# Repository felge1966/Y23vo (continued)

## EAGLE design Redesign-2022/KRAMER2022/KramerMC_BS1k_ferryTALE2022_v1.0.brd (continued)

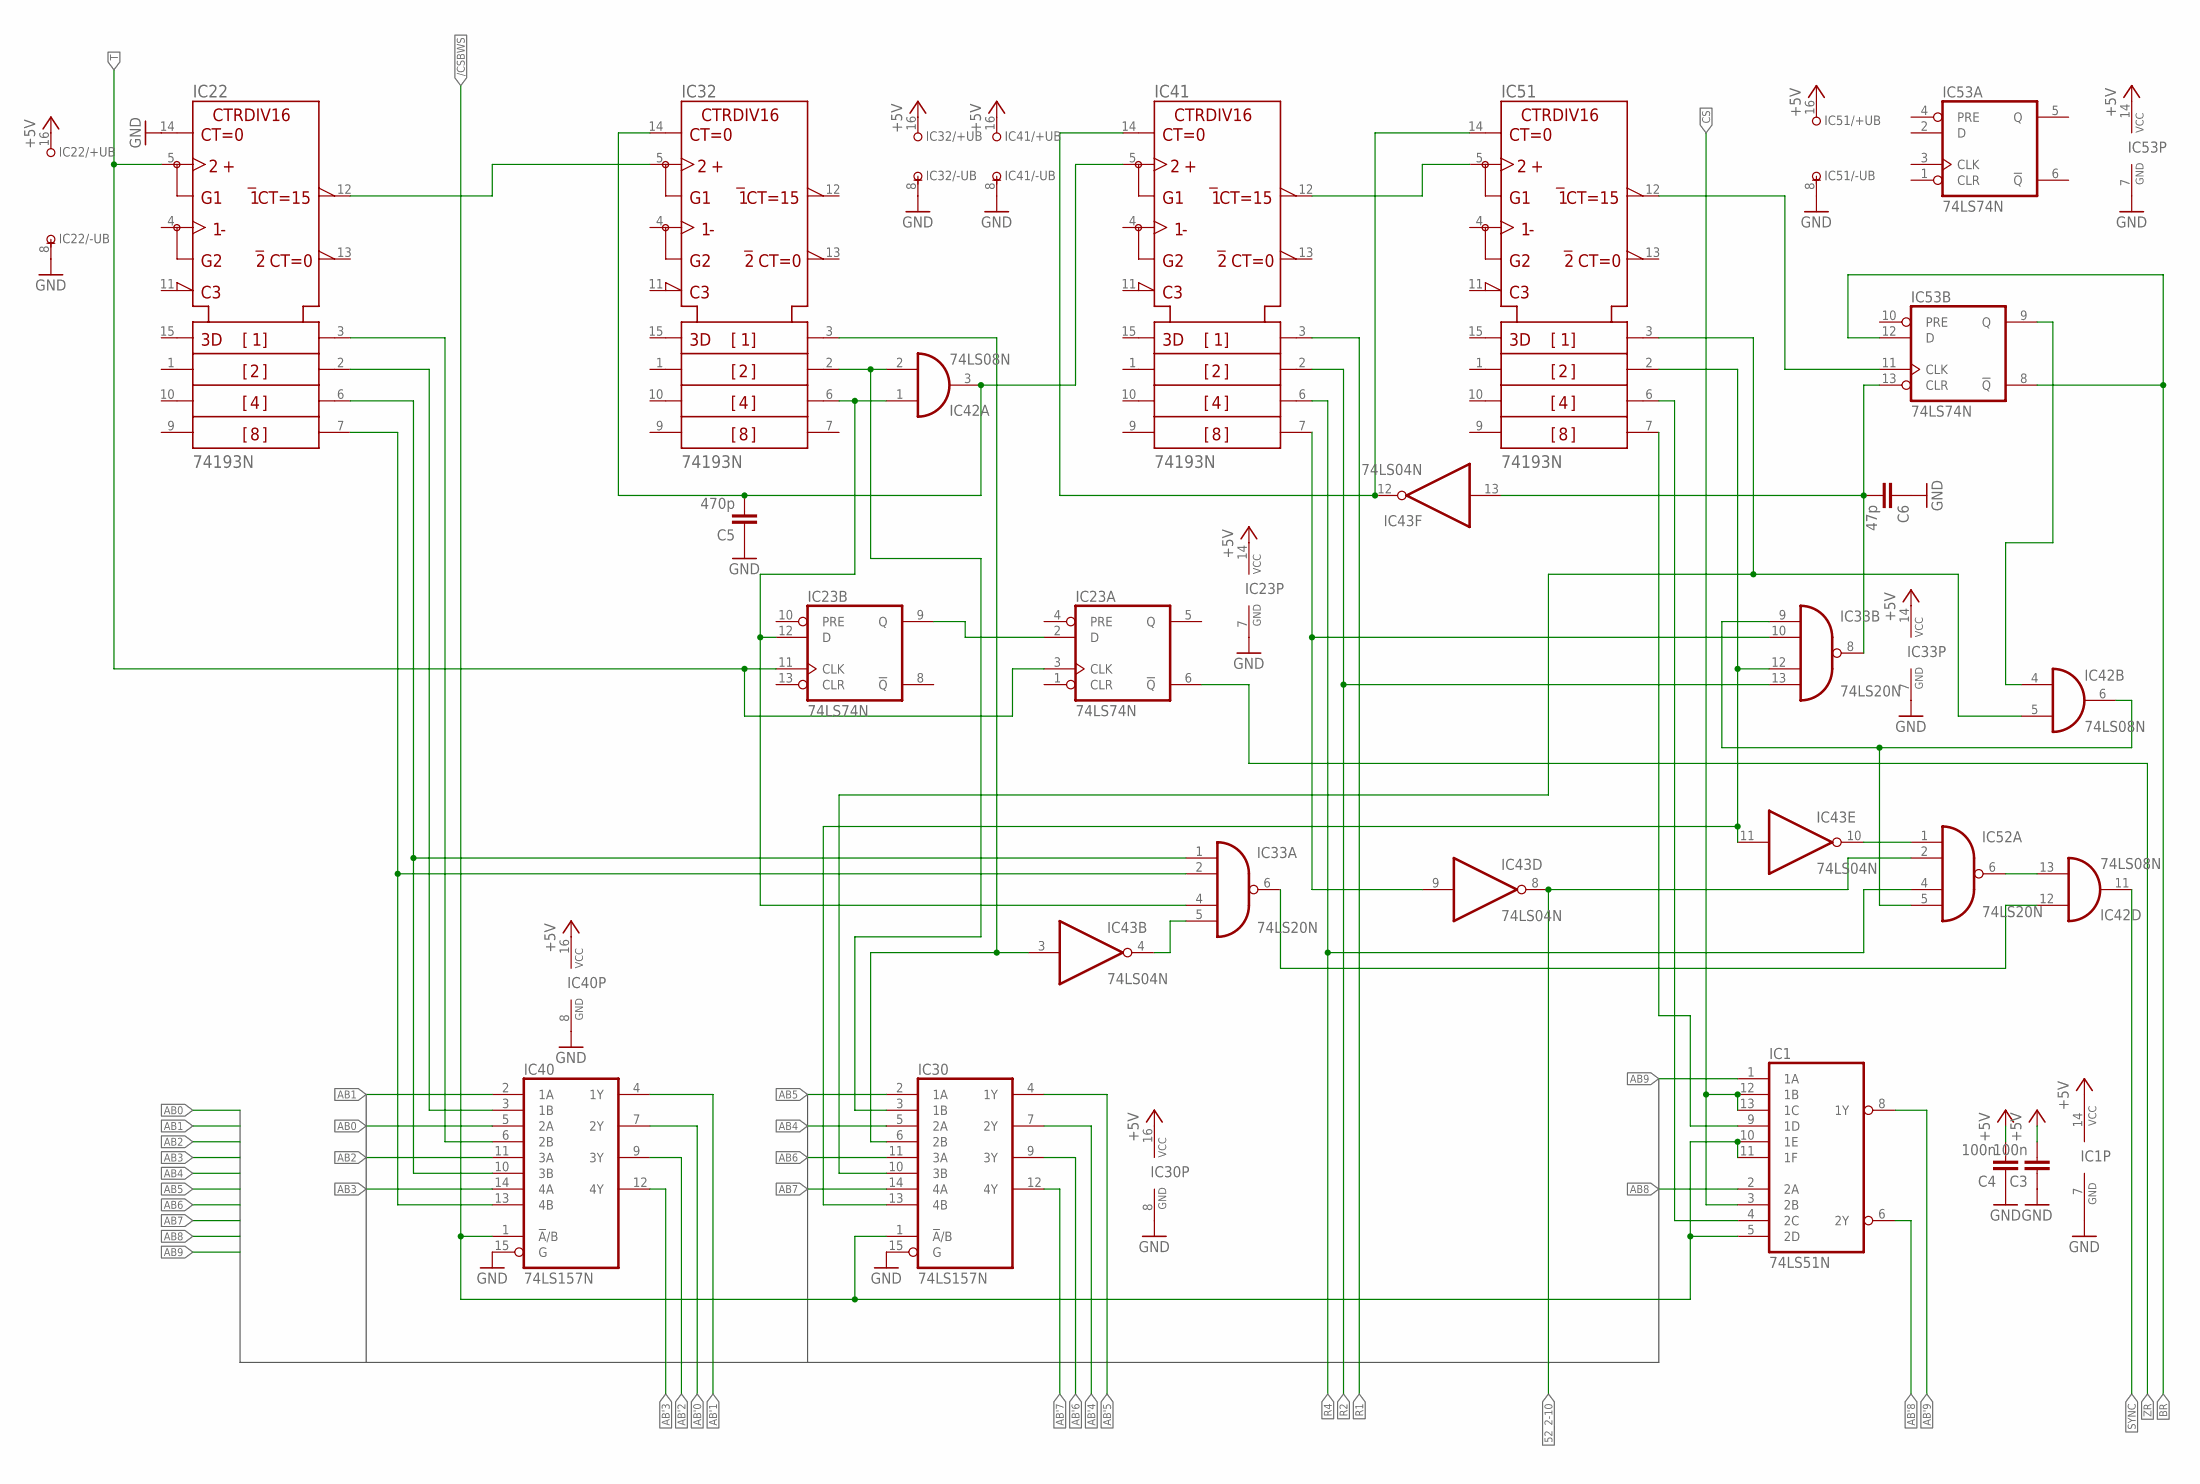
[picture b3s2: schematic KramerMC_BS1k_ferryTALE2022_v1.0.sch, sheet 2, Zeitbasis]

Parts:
C3, C4: 100n; C050-024X044
C5: 470p; C050-024X044
C6: 47p; C050-024X044
IC1: 74LS51N; DIL14
IC22, IC32, IC41, IC51: 74193N; DIL16
IC23, IC53: 74LS74N; DIL14
IC30, IC40: 74LS157N; DIL16
IC33, IC52: 74LS20N; DIL14
IC42: 74LS08N; DIL14
IC43: 74LS04N; DIL14

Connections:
52_2-10: IC43.8 (O), IC52.2 (I1); also elsewhere on the board
+5V: C3.2, C4.2, IC1.14 (VCC), IC22.16 (+UB), IC23.14 (VCC), IC30.16 (VCC), IC32.16 (+UB), IC33.14 (VCC), IC40.16 (VCC), IC41.16 (+UB), IC51.16 (+UB), IC53.14 (VCC); also elsewhere on the board
/CSBWS: IC1.5 (2D), IC1.10 (1E), IC1.11 (1F), IC30.1 (!A!/B), IC40.1 (!A!/B); also elsewhere on the board
AB0: IC40.5 (2A); also elsewhere on the board
AB1: IC40.2 (1A); also elsewhere on the board
AB2: IC40.11 (3A); also elsewhere on the board
AB3: IC40.14 (4A); also elsewhere on the board
AB4: IC30.5 (2A); also elsewhere on the board
AB5: IC30.2 (1A); also elsewhere on the board
AB6: IC30.11 (3A); also elsewhere on the board
AB7: IC30.14 (4A); also elsewhere on the board
AB8: IC1.2 (2A); also elsewhere on the board
AB9: IC1.1 (1A); also elsewhere on the board
AB'0: IC40.7 (2Y); also elsewhere on the board
AB'1: IC40.4 (1Y); also elsewhere on the board
AB'2: IC40.9 (3Y); also elsewhere on the board
AB'3: IC40.12 (4Y); also elsewhere on the board
AB'4: IC30.7 (2Y); also elsewhere on the board
AB'5: IC30.4 (1Y); also elsewhere on the board
AB'6: IC30.9 (3Y); also elsewhere on the board
AB'7: IC30.12 (4Y); also elsewhere on the board
AB'8: IC1.6 (2Y); also elsewhere on the board
AB'9: IC1.8 (1Y); also elsewhere on the board
BR: IC53.8 (!Q), IC53.12 (D); also elsewhere on the board
CS: IC1.3 (2B), IC1.12 (1B), IC1.13 (1C); also elsewhere on the board
GND: C3.1, C4.1, C5.1, C6.1, IC1.7 (GND), IC22.8 (-UB), IC22.14 (CLR), IC23.7 (GND), IC30.8 (GND), IC30.15 (G), IC32.8 (-UB), IC33.7 (GND), IC40.8 (GND), IC40.15 (G), IC41.8 (-UB), IC51.8 (-UB), IC53.7 (GND); also elsewhere on the board
unnamed: IC22.3 (QA), IC40.6 (2B)
unnamed: IC22.2 (QB), IC40.3 (1B)
unnamed: IC22.6 (QC), IC33.1 (I0), IC40.10 (3B)
unnamed: IC22.7 (QD), IC33.2 (I1), IC40.13 (4B)
unnamed: IC22.12 (!CO), IC32.5 (UP)
unnamed: C5.2, IC32.14 (CLR), IC41.5 (UP), IC42.3 (O)
unnamed: IC23.12 (D), IC32.6 (QC), IC33.4 (I2), IC42.1 (I0)
unnamed: IC30.3 (1B), IC32.2 (QB), IC42.2 (I1)
unnamed: IC30.6 (2B), IC32.3 (QA), IC43.3 (I)
unnamed: IC33.5 (I3), IC43.4 (O)
unnamed: IC23.2 (D), IC23.9 (Q)
unnamed: IC41.12 (!CO), IC51.5 (UP)
unnamed: IC41.14 (CLR), IC43.12 (O), IC51.14 (CLR)
unnamed: C6.2, IC33.8 (O), IC43.13 (I), IC53.13 (CLR)
unnamed: IC33.10 (I1), IC41.7 (QD), IC43.9 (I)
unnamed: IC33.9 (I0), IC42.6 (O), IC52.5 (I3)
unnamed: IC51.12 (!CO), IC53.11 (CLK)
unnamed: IC30.10 (3B), IC42.5 (I1), IC51.3 (QA)
unnamed: IC30.13 (4B), IC33.12 (I2), IC43.11 (I), IC51.2 (QB)
unnamed: IC42.4 (I0), IC53.9 (Q)
unnamed: IC1.4 (2C), IC51.6 (QC)
unnamed: IC1.9 (1D), IC51.7 (QD)
unnamed: IC42.13 (I1), IC52.6 (O)
unnamed: IC43.10 (O), IC52.1 (I0)
unnamed: IC33.6 (O), IC42.12 (I0)
R1: IC41.3 (QA); also elsewhere on the board
R2: IC33.13 (I3), IC41.2 (QB); also elsewhere on the board
R4: IC41.6 (QC), IC52.4 (I2); also elsewhere on the board
SYNC: IC42.11 (O); also elsewhere on the board
T: IC22.5 (UP), IC23.3 (CLK), IC23.11 (CLK); also elsewhere on the board
ZR: IC23.6 (!Q); also elsewhere on the board

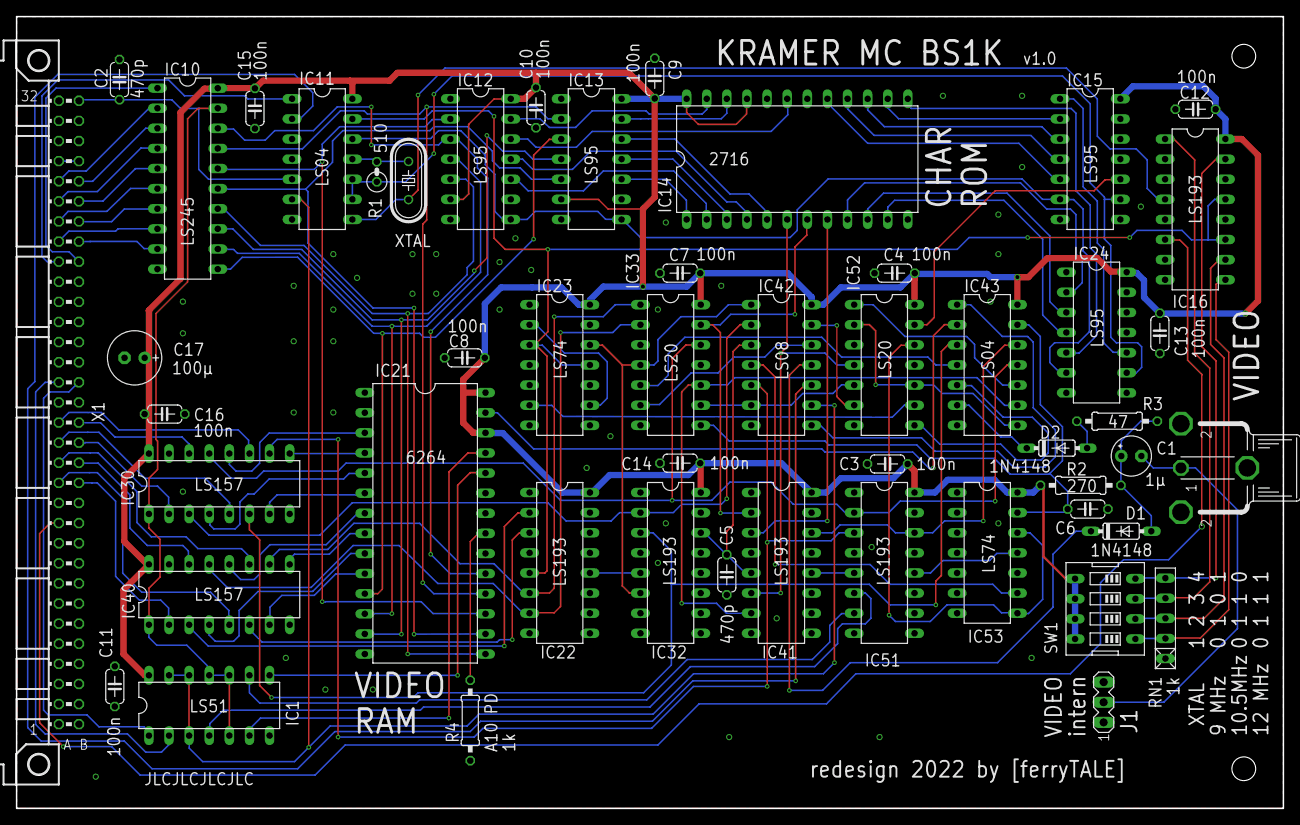
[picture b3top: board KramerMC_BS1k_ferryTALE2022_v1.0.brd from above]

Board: 2 copper layers, 160.0 x 100.0 mm, 51 parts (0 on the bottom side), 112 nets.

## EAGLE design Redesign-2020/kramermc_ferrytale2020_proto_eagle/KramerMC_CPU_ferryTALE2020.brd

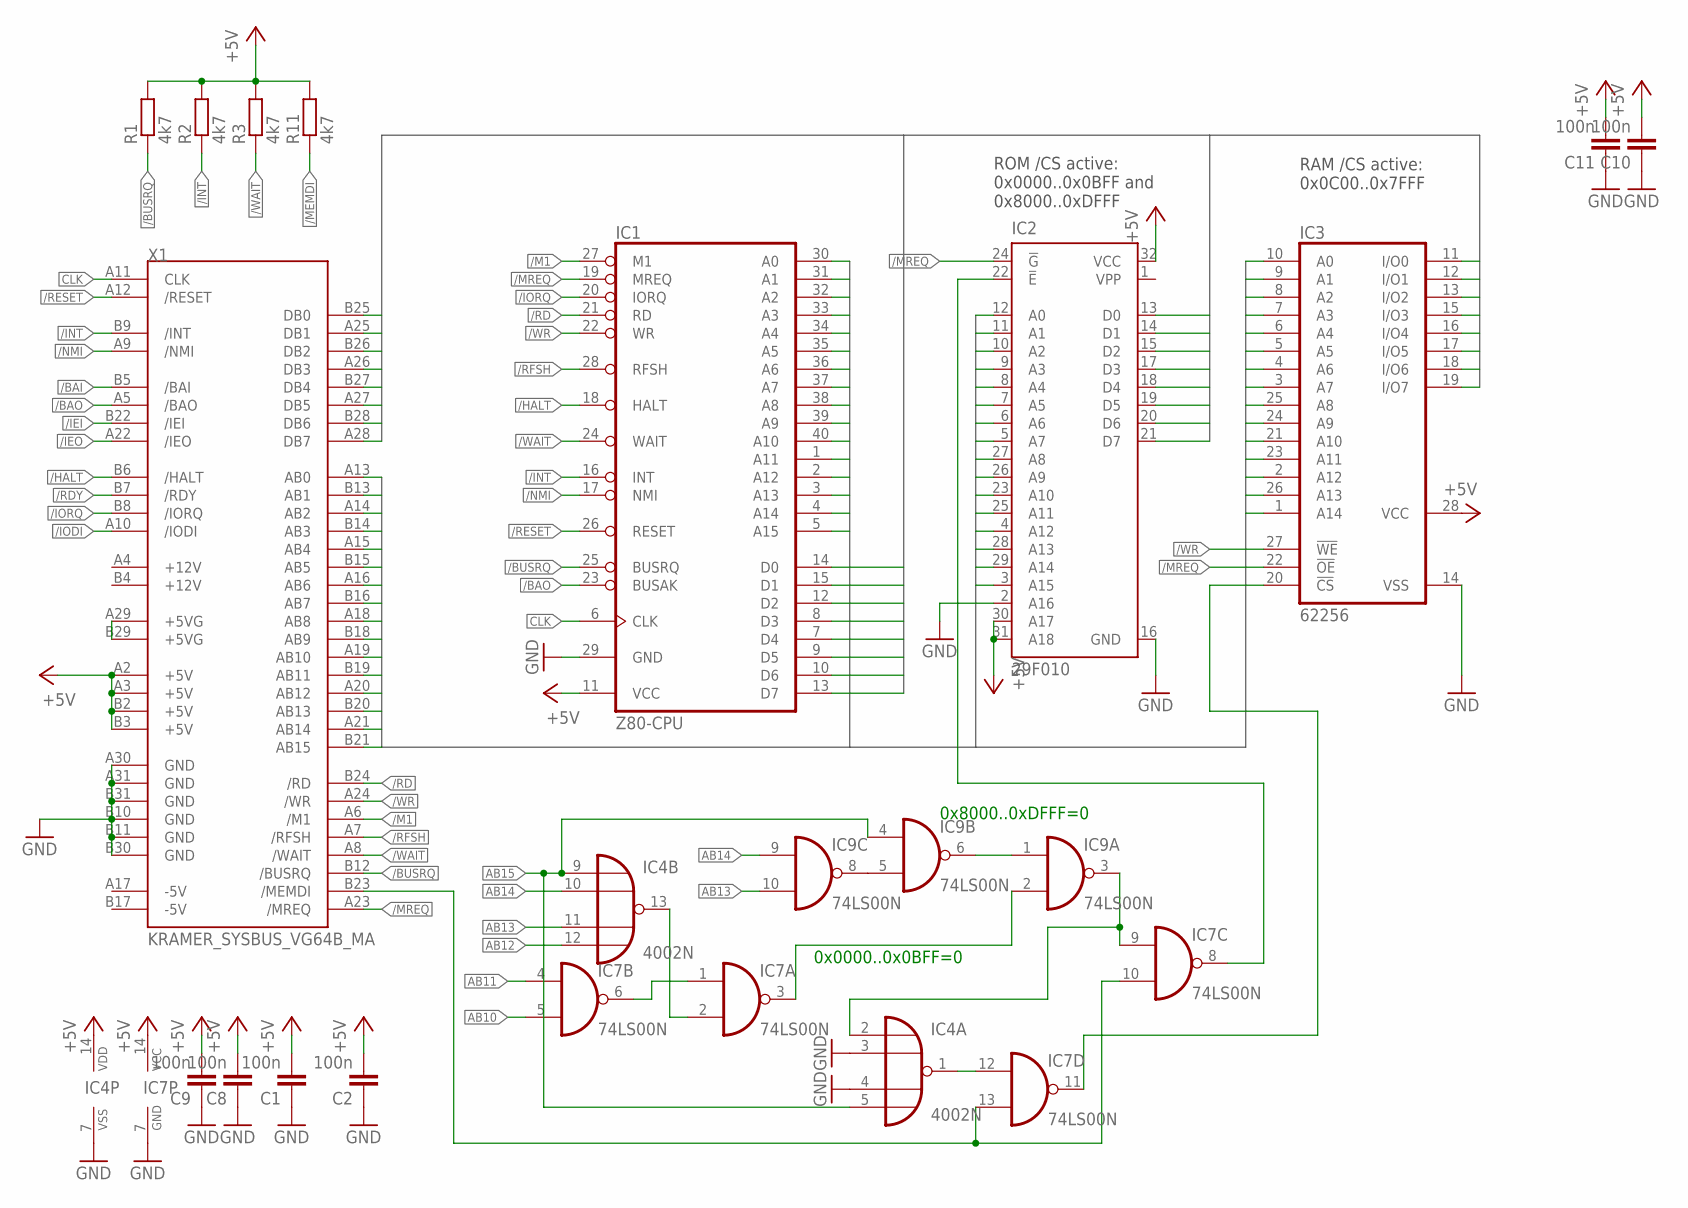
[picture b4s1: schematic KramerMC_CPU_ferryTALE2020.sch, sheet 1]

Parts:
C1, C2, C11: 100n; C0603_NEW
C8: 100n; C050-025X075
C9, C10: 100n; C050-024X044
IC1: Z80-CPU; DIL40
IC2: 29F010; DIL32
IC3: 62256; DIL28-6
IC4: 4002N; DIL14
IC7, IC9: 74LS00N; DIL14
R1, R3: 4k7; R0603_NEW
R2: 4k7; 0207/10
R11: 4k7; R0805_WIDE
X1: KRAMER_SYSBUS_VG64B_MA; MAB64

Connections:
+5V: C1.2, C2.2, C8.2, C9.2, C10.2, C11.2, IC1.11 (VCC), IC2.30 (A17), IC2.31 (A18), IC2.32 (VCC), IC3.28 (VCC), IC4.14 (VDD), IC7.14 (VCC), R1.2, R2.2, R3.2, R11.2, X1.A2 (+5V), X1.A3 (+5V), X1.B2 (+5V), X1.B3 (+5V); also elsewhere on the board
+5VG: X1.A29 (+5VG), X1.B29 (+5VG)
/BAI: X1.B5 (/BAI)
/BAO: IC1.23 (BUSAK), X1.A5 (/BAO)
/BUSRQ: IC1.25 (BUSRQ), R1.1, X1.B12 (/BUSRQ)
/HALT: IC1.18 (HALT), X1.B6 (/HALT)
/IEI: X1.B22 (/IEI)
/IEO: X1.A22 (/IEO)
/INT: IC1.16 (INT), R2.1, X1.B9 (/INT); also elsewhere on the board
/IODI: X1.A10 (/IODI)
/IORQ: IC1.20 (IORQ), X1.B8 (/IORQ); also elsewhere on the board
/M1: IC1.27 (M1), X1.A6 (/M1); also elsewhere on the board
/MEMDI: IC7.10 (I1), IC7.13 (I1), R11.1, X1.B23 (/MEMDI)
/MREQ: IC1.19 (MREQ), IC2.24 (!G), IC3.22 (!OE), X1.A23 (/MREQ)
/NMI: IC1.17 (NMI), X1.A9 (/NMI); also elsewhere on the board
/RD: IC1.21 (RD), X1.B24 (/RD); also elsewhere on the board
/RDY: X1.B7 (/RDY)
/RESET: IC1.26 (RESET), X1.A12 (/RESET); also elsewhere on the board
/RFSH: IC1.28 (RFSH), X1.A7 (/RFSH)
/WAIT: IC1.24 (WAIT), R3.1, X1.A8 (/WAIT)
/WR: IC1.22 (WR), IC3.27 (!WE), X1.A24 (/WR)
AB0: IC1.30 (A0), IC2.12 (A0), IC3.10 (A0), X1.A13 (AB0); also elsewhere on the board
AB1: IC1.31 (A1), IC2.11 (A1), IC3.9 (A1), X1.B13 (AB1); also elsewhere on the board
AB2: IC1.32 (A2), IC2.10 (A2), IC3.8 (A2), X1.A14 (AB2)
AB3: IC1.33 (A3), IC2.9 (A3), IC3.7 (A3), X1.B14 (AB3)
AB4: IC1.34 (A4), IC2.8 (A4), IC3.6 (A4), X1.A15 (AB4)
AB5: IC1.35 (A5), IC2.7 (A5), IC3.5 (A5), X1.B15 (AB5)
AB6: IC1.36 (A6), IC2.6 (A6), IC3.4 (A6), X1.A16 (AB6); also elsewhere on the board
AB7: IC1.37 (A7), IC2.5 (A7), IC3.3 (A7), X1.B16 (AB7); also elsewhere on the board
AB8: IC1.38 (A8), IC2.27 (A8), IC3.25 (A8), X1.A18 (AB8)
AB9: IC1.39 (A9), IC2.26 (A9), IC3.24 (A9), X1.B18 (AB9)
AB10: IC1.40 (A10), IC2.23 (A10), IC3.21 (A10), IC7.5 (I1), X1.A19 (AB10)
AB11: IC1.1 (A11), IC2.25 (A11), IC3.23 (A11), IC7.4 (I0), X1.B19 (AB11)
AB12: IC1.2 (A12), IC2.4 (A12), IC3.2 (A12), IC4.12 (I3), X1.A20 (AB12)
AB13: IC1.3 (A13), IC2.28 (A13), IC3.26 (A13), IC4.11 (I2), IC9.10 (I1), X1.B20 (AB13)
AB14: IC1.4 (A14), IC2.29 (A14), IC3.1 (A14), IC4.10 (I1), IC9.9 (I0), X1.A21 (AB14)
AB15: IC1.5 (A15), IC2.3 (A15), IC4.5 (I3), IC4.9 (I0), IC9.4 (I0), X1.B21 (AB15)
CLK: IC1.6 (CLK), X1.A11 (CLK); also elsewhere on the board
DB0: IC1.14 (D0), IC2.13 (D0), IC3.11 (I/O0), X1.B25 (DB0); also elsewhere on the board
DB1: IC1.15 (D1), IC2.14 (D1), IC3.12 (I/O1), X1.A25 (DB1); also elsewhere on the board
DB2: IC1.12 (D2), IC2.15 (D2), IC3.13 (I/O2), X1.B26 (DB2); also elsewhere on the board
DB3: IC1.8 (D3), IC2.17 (D3), IC3.15 (I/O3), X1.A26 (DB3); also elsewhere on the board
DB4: IC1.7 (D4), IC2.18 (D4), IC3.16 (I/O4), X1.B27 (DB4); also elsewhere on the board
DB5: IC1.9 (D5), IC2.19 (D5), IC3.17 (I/O5), X1.A27 (DB5); also elsewhere on the board
DB6: IC1.10 (D6), IC2.20 (D6), IC3.18 (I/O6), X1.B28 (DB6); also elsewhere on the board
DB7: IC1.13 (D7), IC2.21 (D7), IC3.19 (I/O7), X1.A28 (DB7); also elsewhere on the board
GND: C1.1, C2.1, C8.1, C9.1, C10.1, C11.1, IC1.29 (GND), IC2.2 (A16), IC2.16 (GND), IC3.14 (VSS), IC4.3 (I1), IC4.4 (I2), IC4.7 (VSS), IC7.7 (GND), X1.A30 (GND), X1.A31 (GND), X1.B10 (GND), X1.B11 (GND), X1.B30 (GND), X1.B31 (GND); also elsewhere on the board
unnamed: IC3.20 (!CS), IC7.11 (O)
unnamed: IC7.3 (O), IC9.2 (I1)
unnamed: IC2.22 (!E), IC7.8 (O)
unnamed: IC9.5 (I1), IC9.8 (O)
unnamed: IC9.1 (I0), IC9.6 (O)
unnamed: IC4.2 (I0), IC7.9 (I0), IC9.3 (O)
unnamed: IC4.13 (O), IC7.2 (I1)
unnamed: IC7.1 (I0), IC7.6 (O)
unnamed: IC4.1 (O), IC7.12 (I0)
VPP: IC2.1 (VPP)

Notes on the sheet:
RAM /CS active: 0x0C00..0x7FFF
ROM /CS active: 0x0000..0x0BFF and 0x8000..0xDFFF
0x0000..0x0BFF=0
0x8000..0xDFFF=0

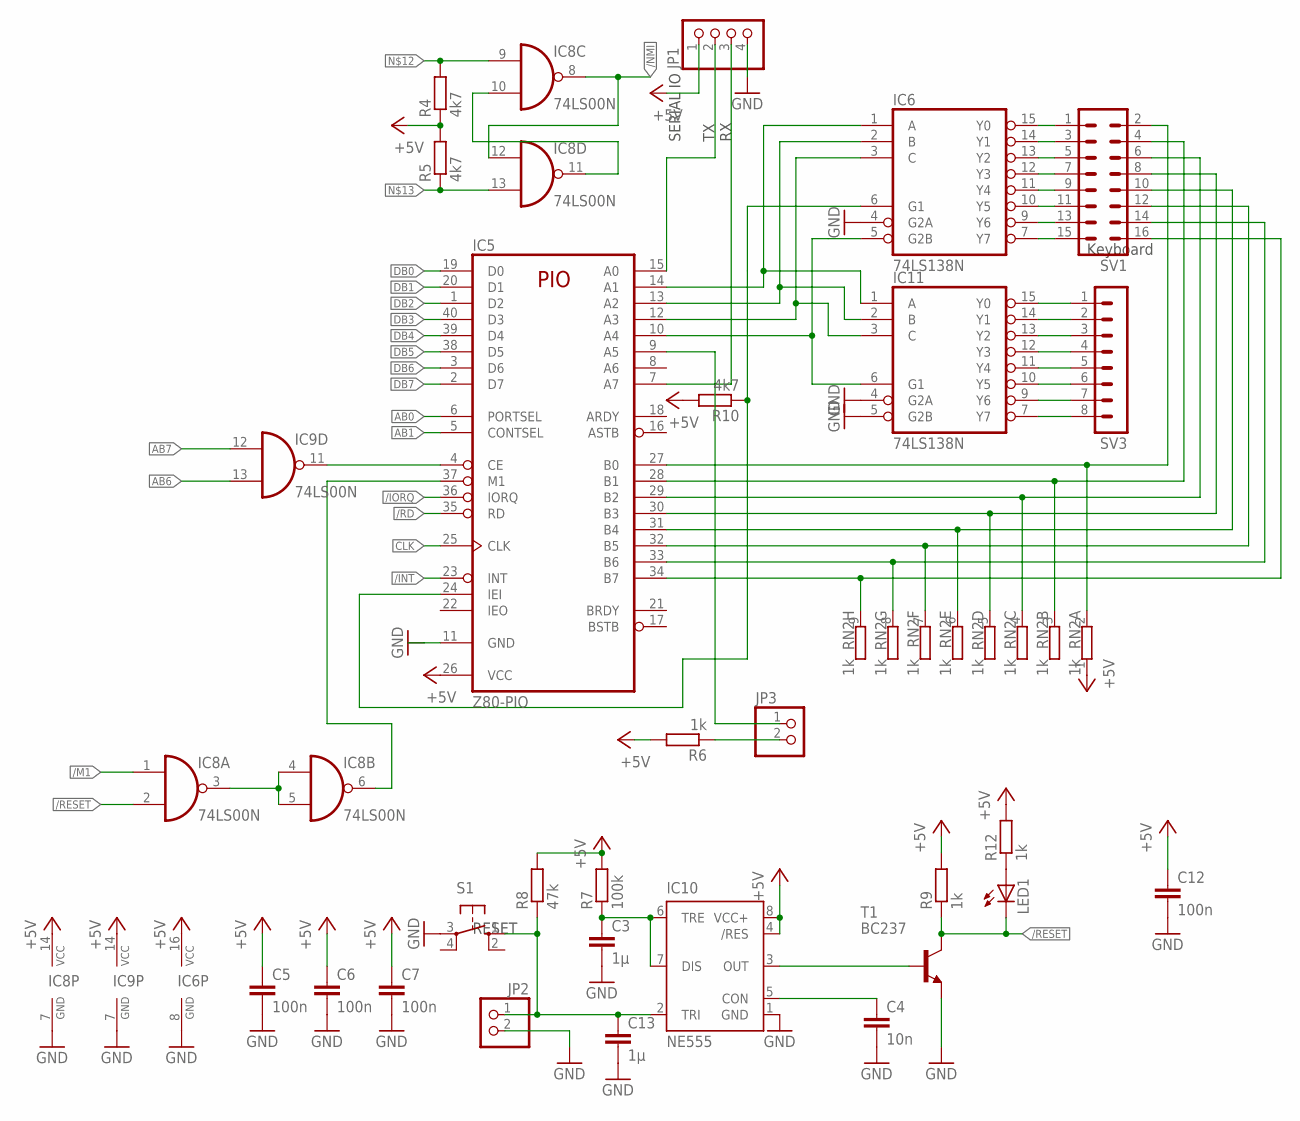
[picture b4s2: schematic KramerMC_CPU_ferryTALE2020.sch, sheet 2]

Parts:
C3, C13: 1µ; C0603_NEW
C4: 10n; C0805
C5, C6, C7, C12: 100n; C0603_NEW
IC5: Z80-PIO; DIL40
IC6, IC11: 74LS138N; DIL16
IC8, IC9: 74LS00N; DIL14
IC10: NE555; DIL-08
JP1: PINHD-1X4/90; 1X04/90
JP2, JP3: PINHD-1X2/90; 1X02/90
LED1: LED3MM
R4, R5: 4k7; R0805
R6: 1k; 0207/10
R7: 100k; R0603_NEW
R8: 47k; R0805
R9, R12: 1k; R0603_NEW
R10: 4k7; 0207/7
RN2: 1k; SIL9
S1: 10-XX; B3F-10XX
SV1: MA08-2W
SV3: MA08-1W
T1: BC237; TO92

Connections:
+5V: C5.1, C6.1, C7.1, C12.1, IC5.26 (VCC), IC6.16 (VCC), IC8.14 (VCC), IC9.14 (VCC), IC10.4 (/RES), IC10.8 (VCC+), JP1.1, R4.1, R5.2, R6.2, R7.2, R8.2, R9.2, R10.2, R12.2, RN2.1; also elsewhere on the board
/INT: IC5.23 (INT); also elsewhere on the board
/IORQ: IC5.36 (IORQ); also elsewhere on the board
/M1: IC8.1 (I0); also elsewhere on the board
/NMI: IC8.8 (O), IC8.12 (I0); also elsewhere on the board
/RD: IC5.35 (RD); also elsewhere on the board
/RESET: IC8.2 (I1), LED1.K (C), R9.1, T1.3 (C); also elsewhere on the board
AB0: IC5.6 (PORTSEL); also elsewhere on the board
AB1: IC5.5 (CONTSEL); also elsewhere on the board
AB6: IC9.13 (I1); also elsewhere on the board
AB7: IC9.12 (I0); also elsewhere on the board
CLK: IC5.25 (CLK); also elsewhere on the board
DB0: IC5.19 (D0); also elsewhere on the board
DB1: IC5.20 (D1); also elsewhere on the board
DB2: IC5.1 (D2); also elsewhere on the board
DB3: IC5.40 (D3); also elsewhere on the board
DB4: IC5.39 (D4); also elsewhere on the board
DB5: IC5.38 (D5); also elsewhere on the board
DB6: IC5.3 (D6); also elsewhere on the board
DB7: IC5.2 (D7); also elsewhere on the board
GND: C3.2, C4.2, C5.2, C6.2, C7.2, C12.2, C13.2, IC5.11 (GND), IC6.4 (G2A), IC6.8 (GND), IC8.7 (GND), IC9.7 (GND), IC10.1 (GND), IC11.4 (G2A), IC11.5 (G2B), IC11.8 (GND), JP1.4, JP2.2, S1.3, T1.1 (E); also elsewhere on the board
unnamed: LED1.A, R12.1
unnamed: IC6.15 (Y0), SV1.1
unnamed: IC8.10 (I1), IC8.11 (O)
unnamed: IC8.9 (I0), R4.2
unnamed: IC8.13 (I1), R5.1
unnamed: IC5.14 (A1), IC6.1 (A), IC11.1 (A)
unnamed: IC5.13 (A2), IC6.2 (B), IC11.2 (B)
unnamed: IC5.12 (A3), IC6.3 (C), IC11.3 (C)
unnamed: IC8.3 (O), IC8.4 (I0), IC8.5 (I1)
unnamed: IC6.14 (Y1), SV1.3
unnamed: IC5.4 (CE), IC9.11 (O)
unnamed: IC5.37 (M1), IC8.6 (O)
unnamed: IC6.13 (Y2), SV1.5
unnamed: IC6.12 (Y3), SV1.7
unnamed: IC6.11 (Y4), SV1.9
unnamed: IC6.10 (Y5), SV1.11
unnamed: IC6.9 (Y6), SV1.13
unnamed: IC6.7 (Y7), SV1.15
unnamed: IC5.27 (B0), RN2.2, SV1.2
unnamed: IC5.28 (B1), RN2.3 (2), SV1.4
unnamed: IC5.29 (B2), RN2.4 (2), SV1.6
unnamed: IC5.30 (B3), RN2.5 (2), SV1.8
unnamed: IC5.31 (B4), RN2.6 (2), SV1.10
unnamed: IC5.32 (B5), RN2.7 (2), SV1.12
unnamed: IC5.33 (B6), RN2.8 (2), SV1.14
unnamed: IC5.34 (B7), RN2.9 (2), SV1.16
unnamed: IC5.9 (A5), JP3.1
unnamed: IC10.3 (OUT), T1.2 (B)
unnamed: C3.1, IC10.6 (TRE), IC10.7 (DIS), R7.1
unnamed: C4.1, IC10.5 (CON)
unnamed: JP3.2, R6.1
unnamed: IC5.24 (IEI), IC6.6 (G1), R10.1
unnamed: IC5.10 (A4), IC6.5 (G2B), IC11.6 (G1)
unnamed: IC11.15 (Y0), SV3.1
unnamed: IC11.14 (Y1), SV3.2
unnamed: IC11.13 (Y2), SV3.3
unnamed: IC11.12 (Y3), SV3.4
unnamed: IC11.11 (Y4), SV3.5
unnamed: IC11.10 (Y5), SV3.6
unnamed: IC11.9 (Y6), SV3.7
unnamed: IC11.7 (Y7), SV3.8
RESET_BUTTON: C13.1, IC10.2 (TRI), JP2.1, R8.1, S1.1 (S)
RX: IC5.7 (A7), JP1.3
TX: IC5.15 (A0), JP1.2
VCC: IC11.16 (VCC)

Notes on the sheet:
SERIAL IO TX RX
Keyboard
RESET

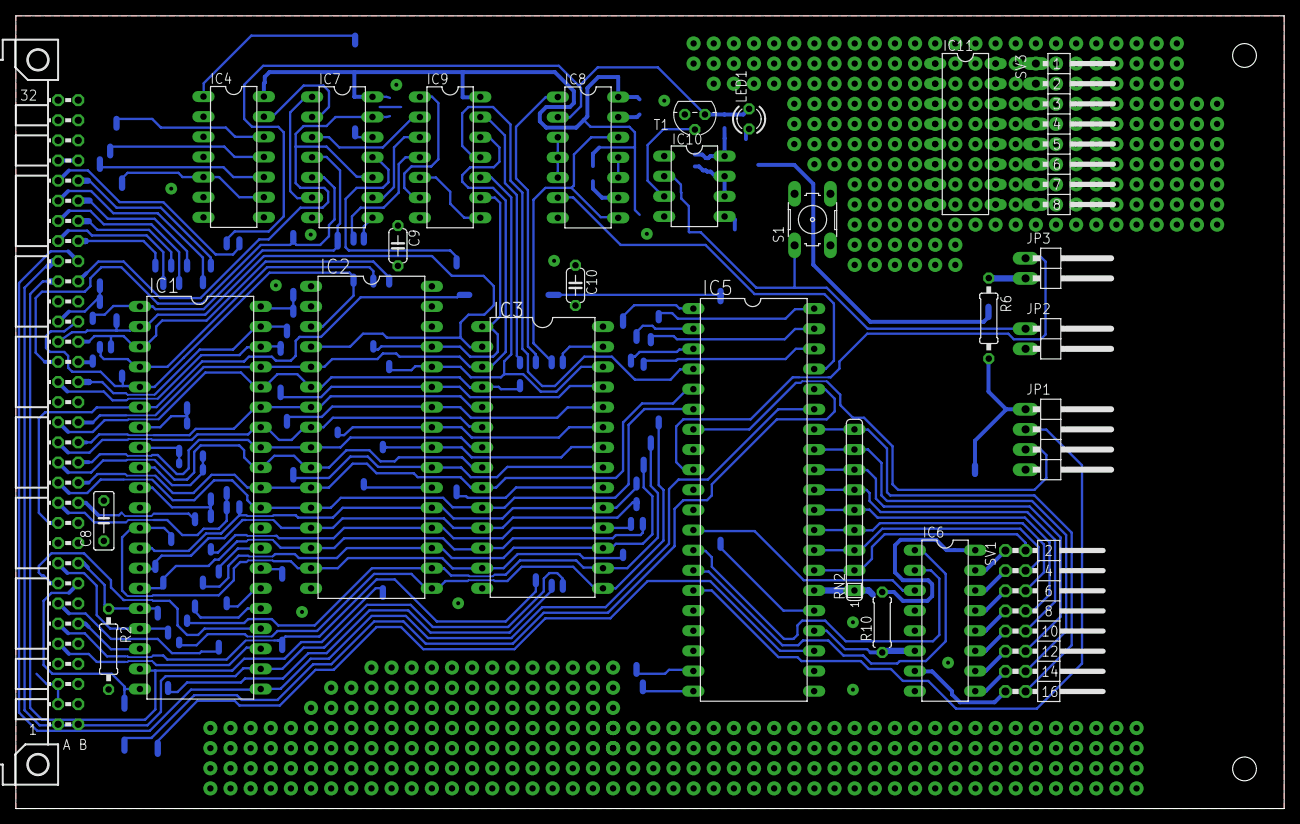
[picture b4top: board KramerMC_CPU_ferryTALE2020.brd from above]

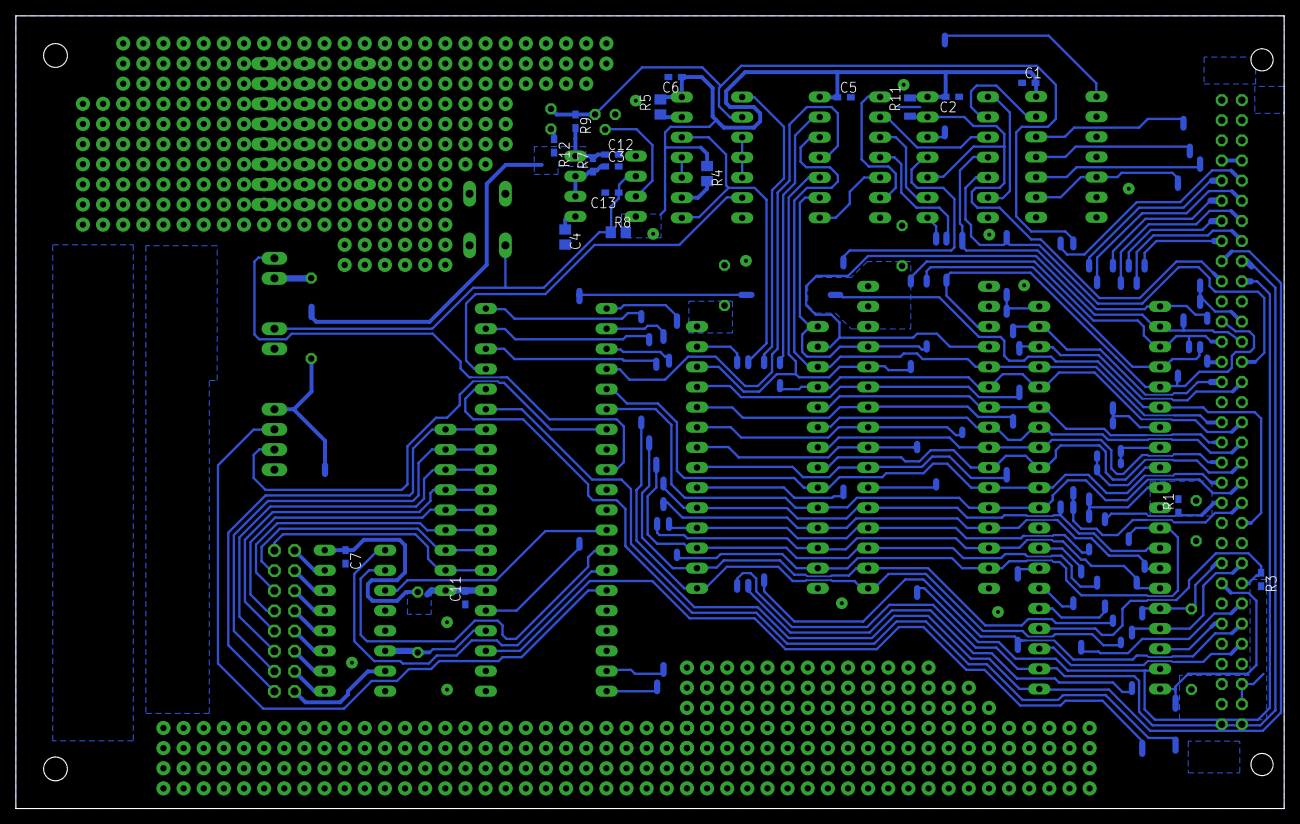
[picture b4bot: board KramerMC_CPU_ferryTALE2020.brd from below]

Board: 2 copper layers, 160.0 x 100.0 mm, 46 parts (19 on the bottom side), 95 nets.
